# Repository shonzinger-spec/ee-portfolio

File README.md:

# EE Portfolio - Shon Zinger

Electrical engineering projects by Shon Zinger, a York University EE graduate. Each project is fully virtual and reproducible with free tools: a standalone Python model runs with numpy and matplotlib (project 06 also uses scipy), and the simulation, schematic and firmware checks are documented with real output pasted into the project README. No hardware was built.

## Start here

- 01 - [A small meter that shows how much power a gadget draws](01-smart-power-node/)
- 02 - [A power converter that steps 12 V down to 5 V, controlled by software](02-sync-buck/)
- 03 - [A program that draws a motor start/stop wiring diagram from a parts list](03-ladder-dxf/)
- 04 - [The protection circuit and firmware for a four-cell lithium-ion battery pack](04-smart-bms-sim/)
- 05 - [A brushless motor controller, tested against a software model of the motor](05-bldc-hil-sim/)
- 06 - [The signal processing of a fingertip blood-oxygen sensor, tested on synthetic signals](06-ppg-spo2/)
- 07 - [A risk calculator for a hypothetical insulin pump, using fault trees and Monte Carlo](07-fault-tree-risk/)

Each project folder has a plain-words summary at the top and the full evidence below.

| # | Project | What it shows | Verification |
|---|---|---|---|
| 01 | [Smart power-monitoring IoT node](01-smart-power-node/) | ESP32 + INA219 power monitor on a 5 V / 2 A rail with an SSD1306 display: 50 mOhm Kelvin shunt, register-level driver, two-task FreeRTOS firmware | main.py self-check, LTspice and ngspice 6/6, host test 33/33, KiCad ERC 0 errors, PCB DRC + schematic parity 0 violations (check_pcb.py 13/13), Wokwi live run |
| 02 | [Digital synchronous buck converter](02-sync-buck/) | 12 V to 5 V / 3 A, 200 kHz synchronous buck with discrete FETs, RC snubber and a digital PI loop in C (input and reference feed-forward, DPWM hysteresis, anti-windup, over-current latch) | main.py 59/59, LTspice vs ngspice cross-check, host test 19/19 + negative gate 4/4, KiCad ERC 0 errors |
| 03 | [Ladder-to-DXF schematic generator](03-ladder-dxf/) | NEMA/JIC motor-starter ladder drawn from a device list: automatic device tags, wire numbers and coil/contact cross-references, DXF for any CAD program, BOM and wire list in Excel | main.py self-check, pytest 22/22, ezdxf audit 0 errors |
| 04 | [Smart BMS simulator](04-smart-bms-sim/) | 4S Li-ion pack: equivalent-circuit and thermal-runaway cell model, BMS firmware in C with OV/UV/OCD/SCD/temperature protection, coulomb-counting SoC, passive balancing and a cell-level end of charge | main.py 30/30, host test 34/34 + negative gate 6/6, ngspice 128 corners, KiCad ERC 0 errors |
| 05 | [BLDC motor controller, hardware-in-the-loop](05-bldc-hil-sim/) | 24 V BLDC with Hall 6-step commutation: timer-interrupt PWM in C with firmware dead-time insertion, cascaded speed/current PI on a sampled DC-link shunt, over-current/Hall/stall protection, run against a switch-level inverter and motor model | main.py 26/26, host test 33/33 + negative gate 7/7, ngspice dead-time sweep and full inverter (within 1.5 % of the plant), KiCad ERC 0 errors |
| 06 | [PPG pulse-oximetry engine](06-ppg-spo2/) | Red/IR photoplethysmography DSP in Python: synthetic signals with room-light flicker and motion, ambient subtraction, AC/DC filters, beat tracking with quality checks, ratio-of-ratios calibration fitted on one synthetic desaturation cohort and tested on another, SpO2 and pulse rate with status flags | main.py 28/28, pytest 47/47, negative gate 10/15 (the five overlapping motion checks are caught together), A_rms 1.34 % on 10 held-out synthetic subjects (ISO 80601-2-61 limit 4.0 %) |
| 07 | [Fault tree and Monte Carlo risk simulator](07-fault-tree-risk/) | ISO 14971 style quantitative risk analysis of a hypothetical insulin pump in Python: fault tree with vote gates and common cause, exact BDD probabilities, drift / wear-out / latent-fault models, Monte Carlo of component state transitions for hazard rates and MTBF, risk evaluation before and after one risk control | main.py 23/23, pytest 68/68, negative gate 15/15, Monte Carlo cross-checked against analytic and Markov results (MTBF 12901 h exact vs 12878 h simulated) |

Highlights of project 01:

- INA219 high-side current sensing: shunt sizing, PGA and calibration choices, saturation handling
- FreeRTOS on the ESP32: two pinned tasks, an overwrite-queue mailbox, a mutex-protected I2C bus
- KiCad schematic generated by script, checked with ERC and a netlist check
- Shunt front-end simulated in LTspice and cross-checked in ngspice
- Wokwi live run of the unmodified firmware against a custom INA219 chip model

## Repository conventions

- A dedicated folder per project (`NN-name/`).
- A standalone main file (for example `main.py`) that runs without a complex install chain.
- A Verification section in each project README, with plots, logs and metrics pasted from real runs.
- A three-sentence Engineering why on the project's trade-offs.
- A Credits section stating what the author did and where AI assisted.

Author: Shon Zinger

AI assistance: Claude (Anthropic) helped with parts of each project; the Credits section of each project README says which.

License: MIT, see [LICENSE](LICENSE).

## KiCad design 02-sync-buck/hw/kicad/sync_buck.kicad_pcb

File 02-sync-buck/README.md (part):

# 02 - Digital Synchronous Buck Converter (12 V to 5 V / 3 A)

## In plain words

- **What it is:** a power converter that steps 12 V down to 5 V, like the adapter that turns a car's supply into a phone charge, but with the control loop done in software on a microcontroller (a small programmable chip).
- **Why it matters:** converters like this sit inside nearly every electronic product, and wasting less power as heat means smaller, cooler devices.
- **What was done:** I designed the circuit, wrote the control code in C and laid out the PCB (the green circuit board), then tested them in circuit simulators and software tests. It is simulated only: no hardware was built.
- **Headline result:** in simulation the output ripple is 9 mV p-p and the efficiency is 97.3 % at 3 A (power stage only, gate drive excluded).
- **Try it:** `python3 main.py`

A simulated design of a digitally controlled synchronous buck: 12 V in, 5 V out at up to 3 A, 200 kHz, two discrete 40 V N-MOSFETs driven by a UCC27211 half-bridge driver, 15 uH / 470 uF output filter, RC snubber on the switch node, and an ESP32-class controller closing the loop in C. The controller samples the output (10k / 6.8k divider), the load current (5 mOhm shunt + INA181A3) and the input voltage (47k / 10k divider) at 50 kHz and runs a PI loop on volts with input-voltage and reference feed-forward, an integrator dead band, DPWM hysteresis, anti-windup, a pre-bias-safe soft start and a latching over-current trip. The ESP32 firmware around that controller compiles. A simulator build of it ran on a simulated ESP32 in Wokwi against the host test's power-stage model: soft start, load steps and an over-current trip. The board is laid out in KiCad: 2 layers, DRC clean, Gerbers and drill files exported. Everything is simulation, host tests and design files; no hardware was built.

| Item | Value |
|---|---|
| Input / output | 12 V (10.8 to 13.2 V) / 5.0 V, 3 A |
| Switching | 200 kHz, 400-tick DPWM (80 MHz MCPWM timer), 50 ns dead time |
| Power stage | 2 x 40 V N-MOSFET (about 7 mOhm), 15 uH (DCR 20 mOhm, Isat 6 A), 470 uF polymer + 10 uF X7R, 1.8 ohm + 1 nF snubber |
| Control | PI on volts, Kp 0.02 V/V, Ki 800 V/(V s), 50 kHz, crossover 128 Hz, PM 89 deg, GM 9.1 dB at no load |
| Simulated results | ripple 9 mV p-p, efficiency 97.3 % at 3 A and 98.3 % at 1 A (power stage, gate drive excluded), 2.5 A load step -8.3 % / +8.8 %, recovery 1.3 ms / 2.1 ms |
| Firmware | ESP32, Arduino-ESP32 core 3.2.0. Product build: MCPWM outputs with 50 ns hardware dead time, ADC1 sampling, 50 kHz control task on core 1, over-current and overrun latches (compile-only; never executed, not even in simulation). LEDC build for Wokwi |
| On-target run (Wokwi) | LEDC sim build at 20x time dilation (times are control time): soft start within +/-1 % in 5.4 ms; 0.5 -> 3 -> 0.5 A steps inside +/-10 %; 6.25 A overload: OCP latched 40 us after the first over-limit sample (3 samples) with both gates low; 0 shoot-through in 375,364 dead times |
| PCB | 54 x 40 mm, 2 layers, 1 oz. DRC: 0 violations, 0 unconnected, 0 parity errors. Layout checks: 39/39 (23 of them on sabotaged copies). Gerbers and Excellon drill files |

## Quick start

Python 3.9+ with numpy and matplotlib. The model needs no SPICE, simulator or hardware.

```
pip install numpy matplotlib
python3 main.py
```

It prints a PASS/FAIL self-check (design equations, the model against the LTspice and ngspice logs, LTspice against ngspice, the digital loop margins, and a Python port of the controller against the C host test) and writes docs/img/main_py_buck.png; add `--no-plot` to skip the figure.

Other checks, from this folder:

```
sh sim/run_spice.sh                 # LTspice + ngspice 47, logs to docs/ (about 50 s)
make -C test/host test              # controller host test, model in the loop
make -C test/host negative          # the same test against four broken controllers
cd hw/kicad && python3 gen_schematic.py --export && python3 check_netlist.py
```

Firmware (arduino-cli 1.2.0 with the esp32:esp32 core 3.2.0), from this folder. The first command builds the product (MCPWM). The second builds the Wokwi variant (LEDC) into sim/wokwi/build:

```
arduino-cli compile -b esp32:esp32:esp32 --warnings all --clean --library src/buck_ctrl src/buck_esp32
arduino-cli compile -b esp32:esp32:esp32 --warnings all --clean --library src/buck_ctrl \
  --build-property "compiler.cpp.extra_flags=-DBUCK_PWM_LEDC" \
  --build-property "compiler.c.extra_flags=-DBUCK_PWM_LEDC" \
  --output-dir sim/wokwi/build src/buck_esp32
```

On-target run in Wokwi. It needs a WASI-SDK clang for the power-stage chip and your own free Wokwi CI token. See [sim/wokwi/README_WOKWI.md](sim/wokwi/README_WOKWI.md):

```
sim/wokwi/build_chip.sh --web
cd sim/wokwi && WOKWI_CLI_TOKEN=... wokwi-cli . --scenario buck_steps.test.yaml --timeout 4000 --serial-log-file ../../docs/wokwi_serial.log
```

PCB. Run these with KiCad 10's bundled Python, which provides `pcbnew`; on macOS it is /Applications/KiCad/KiCad.app/Contents/Frameworks/Python.framework/Versions/3.9/bin/python3:

```
cd hw/kicad && python3 gen_pcb.py --export   # board, DRC, Gerbers, drill files, renders
python3 check_pcb.py                          # layout checks and sabotaged copies
```

## Engineering why

The 15 uH inductor keeps ripple at 32 % of the 3 A load and the peak at 3.5 A against a 6 A saturation rating, but the 470 uF output capacitor is sized for load steps rather than the 9 mV ripple, because a PI loop sampled at 50 kHz has to cross over near 130 Hz, far below the 1.9 kHz LC resonance, so the first millisecond of a 2.5 A step is carried by the filter's 0.18 ohm characteristic impedance (an 8 % dip) and not by the controller. Running the PI on volts with input-voltage and reference feed-forward keeps the loop gain constant from 10.8 to 13.2 V and lets soft start follow its ramp, while a 20 mV integrator dead band and 0.75 LSB of duty hysteresis stop the 30 mV DPWM step from pumping that resonance into a limit cycle, at the cost of up to about 20 mV of static error. On the switch node, 40 V FETs and a 1.8 ohm + 1 nF snubber spend about 40 mW (0.3 points of efficiency) to cut the simulated ringing peak from 27.9 V to 22.2 V in LTspice (22.8 V to 20.1 V in ngspice), leaving more than 40 % margin to the 40 V rating.

## Verification

Each block below is copied from the log named above it and was produced by the command shown. All runs were on macOS. The model, SPICE and host-test runs are from 2026-10-27. The schematic ERC, firmware, Wokwi and PCB runs are from 2026-11-03. Everything is simulation, host tests and design checks; no hardware was built.

### Standalone model (main.py)

`python3 main.py` (docs/main_py.log). Exit code 0 means every check passed.

```
Sync buck 02 - main.py (simulated design; no hardware built)
Constants from src/buck_ctrl/buck_config.h: Kp 0.02 V/V, Ki 800 V/(V s), Ts 20 us, DPWM 400 ticks, dead band 20 mV, hysteresis 0.75 LSB

[1] Netlist and firmware constants
  C01 model values = sim/buck_sync.cir           D, L, C7, ESR, DCR, Rsh, dead time           PASS
  C02 firmware fsw / ticks / dead time           200 kHz, 400 ticks, 4 x 12.5 ns = 50 ns      PASS

[2] Design equations (3 A, 12 V)
    D = 0.4167, dIL = 0.972 A p-p (32 % of 3 A), Ipk = 3.49 A, f0 = 1876 Hz, Z0 = 0.177 ohm
  C03 inductor ripple 20-40 % of Iout            32 %                                         PASS
  C04 Ipk <= Isat / 1.2                          3.49 A vs 5.00 A                             PASS
  C05 2.5 A step: Z0 * dI <= 10 % Vout           442 mV (limit 500 mV)                        PASS
  C06 LC resonance > 10 x loop crossover         f0 1876 Hz, fc 127 Hz                        PASS

[3] LTspice vs ngspice (cases: 1 = 3 A, 2 = 1 A, 3 = 3 A no snubber)
  C07 vout_avg case 1                            LT 4.9613  ng 4.965  rel 0.0752 %            PASS
  C07 vout_avg case 2                            LT 5.0457  ng 5.047  rel 0.0272 %            PASS
  C07 il_pp case 1                               LT 0.97635  ng 0.97772  rel 0.14 %           PASS
  C07 il_pp case 2                               LT 0.97872  ng 0.97857  rel 0.0155 %         PASS
  C07 vout_pp case 1                             LT 0.0091524  ng 0.0092951  rel 1.56 %       PASS
  C07 vout_pp case 2                             LT 0.0089283  ng 0.0089842  rel 0.626 %      PASS
  C07 pin case 1                                 LT 15.186  ng 15.207  rel 0.135 %            PASS
  C07 pin case 2                                 LT 5.1814  ng 5.1807  rel 0.0118 %           PASS
  C07 pout case 1                                LT 14.768  ng 14.791  rel 0.15 %             PASS
  C07 pout case 2                                LT 5.0917  ng 5.0945  rel 0.0544 %           PASS
  C07 eff case 1                                 LT 0.9725  ng 0.97264  abs 0.000146          PASS
  C07 eff case 2                                 LT 0.98271  ng 0.98336  abs 0.000651         PASS
  C07 pgate case 1                               LT 0.095451  ng 0.095092  rel 0.376 %        PASS
  C07 pgate case 2                               LT 0.095232  ng 0.095293  rel 0.0637 %       PASS
  C08 LTspice Vsw peak < 0.75 BVdss              max 27.9 V (limit 30 V)                      PASS
  C09 LTspice snubber lowers the Vsw peak        22.2 V with, 27.9 V without                  PASS
  C08 ngspice Vsw peak < 0.75 BVdss              max 22.8 V (limit 30 V)                      PASS
  C09 ngspice snubber lowers the Vsw peak        20.1 V with, 22.8 V without                  PASS

[4] Model vs SPICE
  C10 Vout full 3 A vs LT                        model 4.9619 V, SPICE 4.9613 V               PASS
  C11 dIL p-p full 3 A vs LT                     model 0.981 A, SPICE 0.976 A                 PASS
  C12 Vout ripple full 3 A vs LT                 model 8.91 mV, SPICE 9.15 mV                 PASS
  C13 efficiency full 3 A vs LT                  model 97.34 %, SPICE 97.25 %                 PASS
  C14 gate drive full 3 A vs LT                  model 87 mW, SPICE 95 mW                     PASS
  C15 snubber loss full 3 A vs LT                C Vin^2 fsw 28.8 mW (+/-50 %), SPICE 41.2 mW PASS
  C10 Vout full 3 A vs ng                        model 4.9619 V, SPICE 4.9650 V               PASS
  C11 dIL p-p full 3 A vs ng                     model 0.981 A, SPICE 0.978 A                 PASS
  C12 Vout ripple full 3 A vs ng                 model 8.91 mV, SPICE 9.30 mV                 PASS
  C13 efficiency full 3 A vs ng                  model 97.34 %, SPICE 97.26 %                 PASS
  C14 gate drive full 3 A vs ng                  model 87 mW, SPICE 95 mW                     PASS
  C15 snubber loss full 3 A vs ng                C Vin^2 fsw 28.8 mW (+/-50 %), SPICE 36.7 mW PASS
    loss budget at 3 A (mW): HS conduction 26, LS conduction 34, inductor DCR 179, shunt 44, Cin ESR 6, Cout ESR 1, HS switching 11, dead-time diode 45, reverse recovery 30, snubber 29
  C16 FET Tj at 50 degC ambient < 100 degC       HS 66 mW, LS 79 mW -> Tj 54 degC             PASS
  C17 inductor temperature < 100 degC            179 mW -> 57 degC                            PASS
  C10 Vout light 1 A vs LT                       model 5.0272 V, SPICE 5.0457 V               PASS
  C11 dIL p-p light 1 A vs LT                    model 0.979 A, SPICE 0.979 A                 PASS
  C12 Vout ripple light 1 A vs LT                model 8.94 mV, SPICE 8.93 mV                 PASS
  C13 efficiency light 1 A vs LT                 model 98.27 %, SPICE 98.27 %                 PASS
  C14 gate drive light 1 A vs LT                 model 87 mW, SPICE 95 mW                     PASS
  C15 snubber loss light 1 A vs LT               C Vin^2 fsw 28.8 mW (+/-50 %), SPICE 24.5 mW PASS
  C10 Vout light 1 A vs ng                       model 5.0272 V, SPICE 5.0470 V               PASS
  C11 dIL p-p light 1 A vs ng                    model 0.979 A, SPICE 0.979 A                 PASS
  C12 Vout ripple light 1 A vs ng                model 8.94 mV, SPICE 8.98 mV                 PASS
  C13 efficiency light 1 A vs ng                 model 98.27 %, SPICE 98.34 %                 PASS
  C14 gate drive light 1 A vs ng                 model 87 mW, SPICE 95 mW                     PASS
  C15 snubber loss light 1 A vs ng               C Vin^2 fsw 28.8 mW (+/-50 %), SPICE 24.7 mW PASS

[5] Digital loop (PI + feed-forward, 50 kHz, 1-sample delay)
  C18 margins 0.01 A                             fc 128 Hz, PM 89 deg, GM 9.1 dB              PASS
  C18 margins 1 A                                fc 127 Hz, PM 89 deg, GM 10.5 dB             PASS
  C18 margins 3 A                                fc 126 Hz, PM 89 deg, GM 12.9 dB             PASS
  C18 margins 0.01 A, L +20 %                    fc 128 Hz, PM 89 deg, GM 7.6 dB              PASS
  C18 margins 0.01 A, C -20 %                    fc 128 Hz, PM 90 deg, GM 8.9 dB              PASS
  C18 margins 0.01 A, L -20 % C +20 %            fc 128 Hz, PM 89 deg, GM 11.0 dB             PASS

[6] Python port of the controller vs the C host test
  C19 host test log RESULT all PASS              19/19                                        PASS
  C20 0.5 -> 3 A dip: Python vs C                Python 4.5864 V, C 4.5864 V                  PASS
  C21 3 -> 0.5 A peak: Python vs C               Python 5.4419 V, C 5.4419 V                  PASS

RESULT: 59/59 PASS
figure: docs/img/main_py_buck.png
```

*main.py: modelled inductor current and output ripple at 3 A (top left), efficiency from the loss budget with the LTspice and ngspice points (top right), digital loop gain at three loads (bottom left), and the Python port of the controller through soft start and the 2.5 A load steps (bottom right).*

### LTspice power stage

`sh sim/run_spice.sh` runs `LTspice -b sim/buck_sync.cir` (open loop, fixed duty 0.4195, three stepped cases: 1 = 3 A, 2 = 1 A, 3 = 3 A without snubber, measured over 1.00 to 1.05 ms after starting from the settled operating point). Measurement section of docs/sim_ltspice.log (the script converts LTspice's UTF-16 log to UTF-8):

```
Measurement: vout_avg
  step	AVG(v(vload))	FROM	TO
     1	4.96132	0.001	0.00105
     2	5.04566	0.001	0.00105
     3	4.95987	0.001	0.00105

Measurement: vout_pp
  step	PP(v(vload))	FROM	TO
     1	0.00915241	0.001	0.00105
     2	0.0089283	0.001	0.00105
     3	0.00914478	0.001	0.00105

Measurement: il_avg
  step	AVG(i(l1))	FROM	TO
     1	2.97249	0.001	0.00105
     2	1.00848	0.001	0.00105
     3	2.97174	0.001	0.00105

Measurement: il_pp
  step	PP(i(l1))	FROM	TO
     1	0.976345	0.001	0.00105
     2	0.978718	0.001	0.00105
     3	0.976289	0.001	0.00105

Measurement: pin
  step	AVG(-v(vsrc)*i(v1))	FROM	TO
     1	15.1862	0.001	0.00105
     2	5.18135	0.001	0.00105
     3	15.1747	0.001	0.00105

Measurement: pout
  step	AVG(v(vload)*v(vload)/rload)	FROM	TO
     1	14.7685	0.001	0.00105
     2	5.09174	0.001	0.00105
     3	14.7599	0.001	0.00105

Measurement: pgate
  step	AVG(-(v(ghd,sw)*i(vgh)+v(gld)*i(vgl)))	FROM	TO
     1	0.0954512	0.001	0.00105
     2	0.0952321	0.001	0.00105
     3	0.0945081	0.001	0.00105

Measurement: psnub
  step	AVG(v(sw,snb)*i(rsn))	FROM	TO
     1	0.0411916	0.001	0.00105
     2	0.0244952	0.001	0.00105
     3	6.20517e-10	0.001	0.00105

Measurement: vsw_max
  step	MAX(v(sw))	FROM	TO
     1	22.2205	0.001	0.00105
     2	17.8984	0.001	0.00105
     3	27.9306	0.001	0.00105

Measurement: eff
  step	pout/pin
     1	0.972498
     2	0.982705
     3	0.972665
```

### ngspice 47 cross-check

The same circuit and VDMOS card in ngspice dialect (sim/ngspice/buck_sync_ngspice.cir): the `.step`/`table()` sweep becomes a control-block loop with `alterparam` + `reset`, and the measurements move into the control block. Measurement lines of docs/sim_ngspice.log (`grep -E "^step|^[a-z_]+ += " docs/sim_ngspice.log`):

```
step 1 RLOAD=1.6667 SNUB=1
vout_avg            =  4.96505e+00 from=  1.00000e-03 to=  1.05000e-03
vout_pp             =  9.29507e-03 from=  1.00000e-03 to=  1.05000e-03
il_avg              =  2.97308e+00 from=  1.00000e-03 to=  1.05000e-03
il_pp               =  9.77716e-01 from=  1.00000e-03 to=  1.05000e-03
pin                 =  1.52067e+01 from=  1.00000e-03 to=  1.05000e-03
pout                =  1.47907e+01 from=  1.00000e-03 to=  1.05000e-03
pgate               =  9.50925e-02 from=  1.00000e-03 to=  1.05000e-03
psnub               =  3.66659e-02 from=  1.00000e-03 to=  1.05000e-03
vsw_max             =  2.01266e+01 at=  1.04506e-03
eff = 0.972644
step 2 RLOAD=5 SNUB=1
vout_avg            =  5.04703e+00 from=  1.00000e-03 to=  1.05000e-03
vout_pp             =  8.98421e-03 from=  1.00000e-03 to=  1.05000e-03
il_avg              =  1.00808e+00 from=  1.00000e-03 to=  1.05000e-03
il_pp               =  9.78566e-01 from=  1.00000e-03 to=  1.05000e-03
pin                 =  5.18074e+00 from=  1.00000e-03 to=  1.05000e-03
pout                =  5.09451e+00 from=  1.00000e-03 to=  1.05000e-03
pgate               =  9.52928e-02 from=  1.00000e-03 to=  1.05000e-03
psnub               =  2.47471e-02 from=  1.00000e-03 to=  1.05000e-03
vsw_max             =  1.76416e+01 at=  1.02006e-03
eff = 0.983356
step 3 RLOAD=1.6667 SNUB=0
vout_avg            =  4.96347e+00 from=  1.00000e-03 to=  1.05000e-03
vout_pp             =  9.22277e-03 from=  1.00000e-03 to=  1.05000e-03
il_avg              =  2.97294e+00 from=  1.00000e-03 to=  1.05000e-03
il_pp               =  9.77638e-01 from=  1.00000e-03 to=  1.05000e-03
pin                 =  1.52103e+01 from=  1.00000e-03 to=  1.05000e-03
pout                =  1.47813e+01 from=  1.00000e-03 to=  1.05000e-03
pgate               =  9.47475e-02 from=  1.00000e-03 to=  1.05000e-03
psnub               =  4.67871e-12 from=  1.00000e-03 to=  1.05000e-03
vsw_max             =  2.27861e+01 at=  1.01506e-03
eff = 0.971796
```

main.py compares the two simulators (check group [3] above): Vout within 0.08 %, inductor ripple within 0.14 %, output ripple within 1.6 %, efficiency within 0.07 points, gate-drive power within 0.4 %. The switch-node peaks differ (27.9 V vs 22.8 V without snubber) because the ringing lasts a few nanoseconds and each simulator resolves it with its own time-step control; both stay below 30 V (75 % of BVdss) and both show the snubber lowering the peak.

### Controller host test (model in the loop)

`make -C test/host test` (docs/host_test.log). The controller (src/buck_ctrl) is compiled for the host with `-Wall -Wextra -Werror` and run against an averaged model of the power stage (test/host/plant.c, same component values as the SPICE decks), with 12-bit ADC quantisation, the 1 nF anti-alias filter, the 400-tick DPWM and a one-period computation delay.

```
./build/test_buck
02 sync buck controller - host test (model in the loop)
Kp 0.02 V/V, Ki 800 V/(V s), Ts 20 us, DPWM 400 ticks, dead band 20 mV, DPWM hysteresis 0.75 LSB, OCP 4.5 A x 3
# closed loop: soft start at 1 A, Vin 12 V
PASS startup overshoot <= 2 %         max 5.0271 V (limit 5.10 V)
PASS startup settle +/-1 % <= 8 ms    5.26 ms (limit 8 ms)
# steady state 1 A, 12-20 ms
PASS dc error <= 0.5 %                mean 5.0081 V (target 5.0 V)
PASS no limit cycle (duty steady)     0 duty-code changes (limit 0)
PASS low-frequency p-p <= 5 mV        0.00 mV (limit 5 mV)
# load step 0.5 -> 3 A at 30 ms, release 3 -> 0.5 A at 45 ms
PASS step dip >= 4.50 V (-10 %)       min 4.5864 V (limit 4.50 V)
PASS step recovery +/-1 % <= 5 ms     1.30 ms (limit 5 ms)
PASS release peak <= 5.50 V (+10 %)   max 5.4419 V (limit 5.50 V)
PASS release recovery +/-1 % <= 5 ms  2.10 ms (limit 5 ms)
# line ramps at 1 A: 12 -> 10.8 V at 65 ms, 10.8 -> 13.2 V at 80 ms (1 ms each)
PASS line deviation <= 2 %            80.8 mV (limit 100 mV)
PASS line recovery +/-1 % <= 5 ms     0.86 ms (limit 5 ms)
# overload 0.8 ohm (6.25 A) at 100 ms
PASS OCP latches within 3 samples     3 samples (limit 3)
PASS inductor peak < Isat 6 A         2.19 A (limit 6.0 A)
PASS stays off after the trip         duty 0, state 3
# unit: integrator windup (output held at 0 V for 20 ms, then 5.5 V)
PASS Vref + integrator <= Dmax x Vin  10.800 V (limit 10.80 V)
PASS unwinds to 50 % within 1.1 x bound 11.96 ms (limit 13.17 ms)
# unit: OCP needs consecutive samples, then latches
PASS 2 + 2 split samples: no trip     state 2 (fault = 3)
PASS 3rd sample trips, start ignored  state 3, fault code 1
# unit: pre-biased start
PASS soft start begins at 3 V pre-bias vref 3.000 V (expected 3.0 V)
RESULT: 19/19 PASS
```

### Negative gate

`make -C test/host negative` (docs/host_negative.log) builds four broken controllers and passes only if the host test fails against every one: M1 without the integrator dead band (limit cycle), M2 with both anti-windup lines deleted (the integrator winds up to 75 V), M3 with the over-current trip out of reach (the inductor reaches 9.7 A), M4 with plain rounding instead of DPWM hysteresis (the load release rings for about 10 ms).

```
== mutant m1 ==
FAIL no limit cycle (duty steady)     5 duty-code changes (limit 0)
FAIL low-frequency p-p <= 5 mV        76.42 mV (limit 5 mV)
RESULT: 17/19 PASS
mutant m1: test FAILED as required
== mutant m2 ==
FAIL Vref + integrator <= Dmax x Vin  74.980 V (limit 10.80 V)
FAIL unwinds to 50 % within 1.1 x bound 40.00 ms (limit 13.17 ms)
RESULT: 17/19 PASS
mutant m2: test FAILED as required
== mutant m3 ==
FAIL OCP latches within 3 samples     -1 samples (limit 3)
FAIL inductor peak < Isat 6 A         9.65 A (limit 6.0 A)
FAIL stays off after the trip         duty 157, state 2
FAIL 3rd sample trips, start ignored  state 1, fault code 0
RESULT: 15/19 PASS
mutant m3: test FAILED as required
== mutant m4 ==
FAIL release recovery +/-1 % <= 5 ms  9.72 ms (limit 5 ms)
RESULT: 18/19 PASS
mutant m4: test FAILED as required
NEGATIVE GATE: 4/4 mutants caught
```

### KiCad ERC and netlist check

`cd hw/kicad && python3 gen_schematic.py --export`, then `kicad-cli sch erc` and `python3 check_netlist.py` (docs/kicad_erc.log; the ERC report also lists four checks set to ignore, as in project 01):

```
# cmd: cd hw/kicad && python3 gen_schematic.py --export
# cmd: kicad-cli sch erc --severity-all -o erc.rpt sync_buck.kicad_sch
# cmd: python3 check_netlist.py
 ** ERC messages: 0  Errors 0  Warnings 0
    - Global label only appears once in the schematic
    - Four connection points are joined together
    - SPICE model issue
    - Assigned footprint doesn't match footprint filters
PASS VIN      C1.1 C2.1 C3.1 C4.1 J1.1 Q1.2 R12.1 U1.1
PASS GND      C1.2 C10.2 C11.2 C12.2 C2.2 C3.2 C4.2 C6.2 C7.2 C8.2 C9.2 J1.2 J2.2 J3.2 Q2.3 R10.2 R11.2 R13.2 R4.2 R8.2 U1.7 U2.2 U2.5
PASS SW       C5.2 L1.1 Q1.3 Q2.2 R3.2 R5.1 U1.4
PASS GH       Q1.1 R1.2 R3.1
PASS GL       Q2.1 R2.2 R4.1
PASS HO       R1.1 U1.3
PASS LO       R2.1 U1.8
PASS HB       C5.1 U1.2
PASS SNB      C6.1 R5.2
PASS VOUT     C7.1 C8.1 L1.2 R6.1
PASS SH_P     R6.2 U2.3
PASS SH_N     R6.3 U2.4
PASS VLOAD    J2.1 R6.4 R7.1
PASS VSENSE   C10.1 J3.5 R7.2 R8.1
PASS VINSENSE C12.1 J3.7 R12.2 R13.1
PASS IAMP     R9.1 U2.1
PASS ISENSE   C11.1 J3.6 R9.2
PASS PWM_H    J3.3 R10.1 U1.5
PASS PWM_L    J3.4 R11.1 U1.6
PASS +3V3     C9.1 J3.1 U2.6
info: 0 single-pin nets (expected 0)
RESULT: PASS
```

*Schematic: KiCad 10, generated by hw/kicad/gen_schematic.py, ERC 0 errors / 0 warnings, netlist check PASS on every net.*

### ESP32 firmware build

The controller is compiled from src/buck_ctrl as a library: one copy, unmodified. With `--warnings all` the compiler prints no warnings for either build. The product build (MCPWM) is in docs/fw_compile_mcpwm.log:

```
# arduino-cli 1.2.0 (esp32:esp32 core 3.2.0), Tue Nov  3 14:16:39 EST 2026
arduino-cli  Version: 1.2.0 Commit: 9c495211 Date: 2025-02-24T15:57:28Z
# cmd: arduino-cli compile -b esp32:esp32:esp32 --warnings all --clean --library src/buck_ctrl src/buck_esp32
Sketch uses 324302 bytes (24%) of program storage space. Maximum is 1310720 bytes.
Global variables use 49348 bytes (15%) of dynamic memory, leaving 278332 bytes for local variables. Maximum is 327680 bytes.
EXIT=0
```

The Wokwi build (LEDC) is in docs/fw_compile_ledc.log. The log ends with a check that the binary rebuilt after the negative runs below matches the one the passing run used:

```
# arduino-cli 1.2.0 (esp32:esp32 core 3.2.0), Tue Nov  3 14:16:14 EST 2026
arduino-cli  Version: 1.2.0 Commit: 9c495211 Date: 2025-02-24T15:57:28Z
# cmd: arduino-cli compile -b esp32:esp32:esp32 --warnings all --clean --library src/buck_ctrl --build-property "compiler.cpp.extra_flags=-DBUCK_PWM_LEDC" --build-property "compiler.c.extra_flags=-DBUCK_PWM_LEDC" --output-dir sim/wokwi/build src/buck_esp32
Sketch uses 313682 bytes (23%) of program storage space. Maximum is 1310720 bytes.
Global variables use 49532 bytes (15%) of dynamic memory, leaving 278148 bytes for local variables. Maximum is 327680 bytes.
EXIT=0
# restore check (Tue Nov  3 14:16:39 EST 2026): cmp of the rebuilt sim/wokwi/build/buck_esp32.ino.bin against the binary that was in place before these runs (the one docs/wokwi_run.log ran):
#   sizes 313824 / 313824 bytes, differing bytes: 70
#   the 70 bytes are at offsets 177-208 (app ELF SHA-256 field), 2671-2677 (build time string) and 313792-313824 (image checksum and SHA-256 trailer); the code and data are identical
```

### On-target run in Wokwi (simulated ESP32)

The LEDC build runs on Wokwi's simulated ESP32 (wokwi-cli 0.29.1).

**The power stage.** It is a Wokwi custom chip, sim/wokwi/buck_plant.chip.c. The chip includes the host test's plant.c, so the run uses the same averaged model and component values as `make -C test/host test`. It works as follows:
- It reads the PWM_H and PWM_L edges.
- It averages each 6.4 us LEDC period into a switch-node voltage. A both-off gap longer than 100 ns lets the body diodes conduct.
- It drives VSENSE, ISENSE and VINSENSE into the ADC pins.
- It measures every dead time and latches its FLT pin on any H/L overlap.

**The scenario.** sim/wokwi/buck_steps.test.yaml repeats the host test:
1. Soft start at 1 A.
2. Load 0.5 -> 3 -> 0.5 A.
3. An overload of 6.25 A, which must latch the OCP with both gates low.

**Time scaling.** Wokwi runs this firmware much slower than real time. One control update costs about 91 us of simulated time. With the 50 kHz interrupt it costs about 500 us (docs/wokwi_timing_diag.log). So the Wokwi build changes the timing:
- The firmware paces the loop on the CPU cycle counter, once every 20 us x 20 of simulated time.
- The chip steps its plant by dt / 20.

Controller and plant therefore still see one update per 20 us. Every firmware time below is control time.

**The ADC.** The Wokwi build reads the ADC through Wokwi's 5 V transfer, one pipelined conversion per update. sim/wokwi/README_WOKWI.md gives the measurements behind each change. None of these changes is in the product build.

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
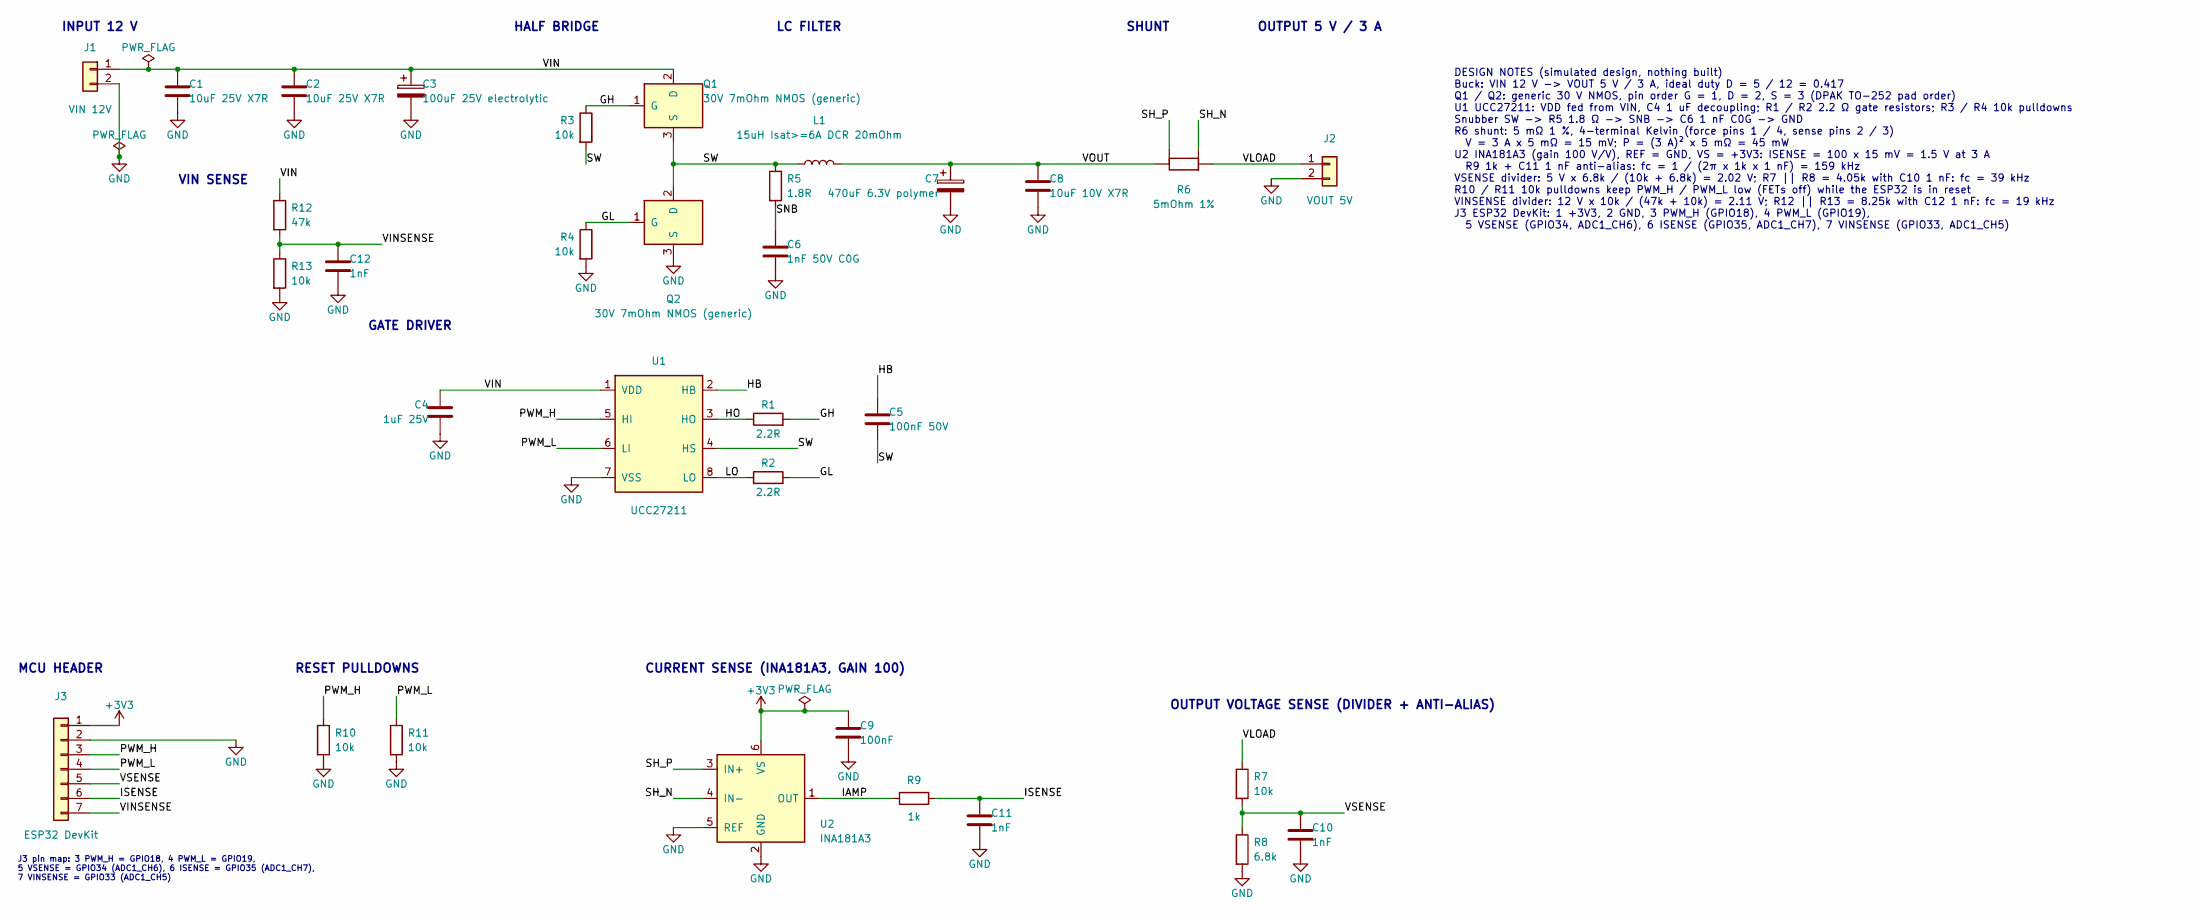
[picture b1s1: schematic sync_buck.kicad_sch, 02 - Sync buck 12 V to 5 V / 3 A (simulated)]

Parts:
C1, C2: 10uF 25V X7R; C_1210_3225Metric
C3: 100uF 25V electrolytic; CP_Radial_D8.0mm_P3.50mm
C4: 1uF 25V; C_0603_1608Metric
C5: 100nF 50V; C_0603_1608Metric
C6: 1nF 50V C0G; C_0603_1608Metric
C7: 470uF 6.3V polymer; CP_Elec_6.3x7.7
C8: 10uF 10V X7R; C_0805_2012Metric
C9: 100nF; C_0603_1608Metric
C10, C11, C12: 1nF; C_0603_1608Metric
J1: VIN 12V; PinHeader_1x02_P2.54mm_Vertical
J2: VOUT 5V; PinHeader_1x02_P2.54mm_Vertical
J3: ESP32 DevKit; PinHeader_1x07_P2.54mm_Vertical
L1: 15uH Isat>=6A DCR 20mOhm; L_Bourns_SRP1245A
Q1, Q2: 30V 7mOhm NMOS (generic); TO-252-3_TabPin2
R1, R2: 2.2R; R_0603_1608Metric
R3, R4, R7, R10, R11, R13: 10k; R_0603_1608Metric
R5: 1.8R; R_0603_1608Metric
R6: 5mOhm 1%; R_Shunt_Vishay_WSK2512_6332Metric_T1.19mm
R8: 6.8k; R_0603_1608Metric
R9: 1k; R_0603_1608Metric
R12: 47k; R_0603_1608Metric
U1: UCC27211; SOIC-8_3.9x4.9mm_P1.27mm
U2: INA181A3; SOT-23-6

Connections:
+3V3: C9.1, J3.1, U2.6 (VS)
/GH: Q1.1 (G), R1.2, R3.1
/GL: Q2.1 (G), R2.2, R4.1
/HB: C5.1, U1.2 (HB)
/HO: R1.1, U1.3 (HO)
/IAMP: R9.1, U2.1 (OUT)
/ISENSE: C11.1, J3.6, R9.2
/LO: R2.1, U1.8 (LO)
/PWM_H: J3.3, R10.1, U1.5 (HI)
/PWM_L: J3.4, R11.1, U1.6 (LI)
/SH_N: R6.3, U2.4 (IN-)
/SH_P: R6.2, U2.3 (IN+)
/SNB: C6.1, R5.2
/SW: C5.2, L1.1, Q1.3 (S), Q2.2 (D), R3.2, R5.1, U1.4 (HS)
/VIN: C1.1, C2.1, C3.1, C4.1, J1.1, Q1.2 (D), R12.1, U1.1 (VDD)
/VINSENSE: C12.1, J3.7, R12.2, R13.1
/VLOAD: J2.1, R6.4, R7.1
/VOUT: C7.1, C8.1, L1.2, R6.1
/VSENSE: C10.1, J3.5, R7.2, R8.1
GND: C1.2, C2.2, C3.2, C4.2, C6.2, C7.2, C8.2, C9.2, C10.2, C11.2, C12.2, J1.2, J2.2, J3.2, Q2.3 (S), R4.2, R8.2, R10.2, R11.2, R13.2, U1.7 (VSS), U2.2 (GND), U2.5 (REF)

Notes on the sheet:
INPUT 12 V
VIN SENSE
HALF BRIDGE
LC FILTER
SHUNT
OUTPUT 5 V / 3 A
GATE DRIVER
MCU HEADER
RESET PULLDOWNS
J3 pin map: 3 PWM_H = GPIO18, 4 PWM_L = GPIO19, 5 VSENSE = GPIO34 (ADC1_CH6), 6 ISENSE = GPIO35 (ADC1_CH7), 7 VINSENSE = GPIO33 (ADC1_CH5)
CURRENT SENSE (INA181A3, GAIN 100)
OUTPUT VOLTAGE SENSE (DIVIDER + ANTI-ALIAS)
DESIGN NOTES (simulated design, nothing built) Buck: VIN 12 V -> VOUT 5 V / 3 A, ideal duty D = 5 / 12 = 0.417 Q1 / Q2: generic 30 V NMOS, pin order G = 1, D = 2, S = 3 (DPAK TO-252 pad order) U1 UCC27211: VDD fed from VIN, C4 1 uF decoupling; R1 / R2 2.2 Ω gate resistors; R3 / R4 10k pulldowns Snu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

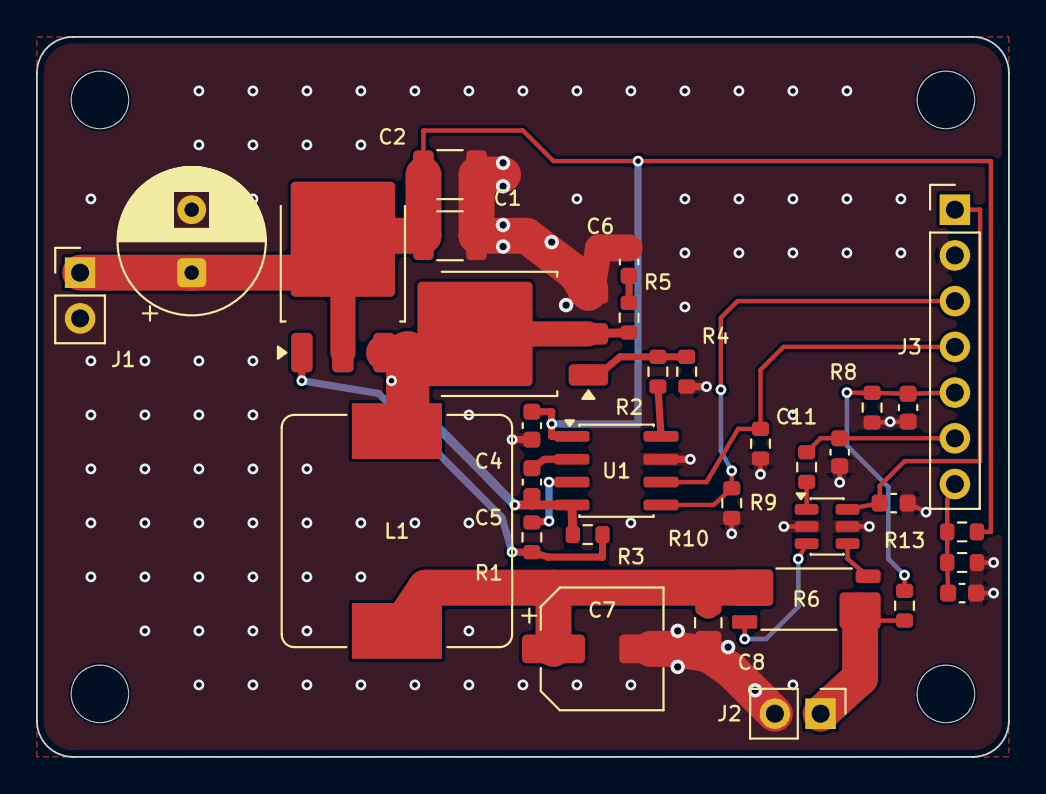
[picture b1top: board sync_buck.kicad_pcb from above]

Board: 2 copper layers, 54.0 x 40.0 mm, 37 parts (0 on the bottom side), 20 nets.

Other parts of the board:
H1, H2, H3, H4: MountingHole_3.2mm_M3

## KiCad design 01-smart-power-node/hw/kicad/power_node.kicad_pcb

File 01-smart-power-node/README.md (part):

# 01 - Smart Power-Monitoring IoT Node (ESP32 + INA219 + SSD1306)

## In plain words

- **What it is:** a small meter that shows how much power a gadget on a 5 V supply draws, built around an ESP32 (a low-cost Wi-Fi microcontroller) and an INA219 (a chip that measures current and voltage) with a small screen.
- **Why it matters:** products from power supplies to smart plugs need to know their own power draw to log it, limit it or warn about faults.
- **What was done:** I designed the measuring circuit, wrote the firmware (the code that runs on the chip) and laid out a PCB (the green circuit board), then checked it all in simulators and software tests. It is simulated only: no hardware was built.
- **Headline result:** at 2 A the 50 mOhm sensing resistor drops 100 mV, and the project's own self-check ends with RESULT: ALL PASS.
- **Try it:** `python3 main.py`

Monitors a 5 V rail at up to 2 A. A high-side 50 mOhm shunt feeds an INA219 set to PGA /4 (+/-160 mV full scale, 3.2 A range, 100 mV at 2 A), with Current_LSB 100 uA/bit, CAL = 8192 and Power_LSB 2 mW. Firmware runs FreeRTOS on the ESP32 Arduino core: sensorTask (priority 3) every 100 ms using vTaskDelayUntil, displayTask (priority 2) every 500 ms, both pinned to core 1. A length-1 queue with xQueueOverwrite/xQueuePeek acts as a latest-value mailbox. A mutex (priority inheritance) serialises the shared 400 kHz I2C bus. The INA219 driver is register-level; no INA219 library is used.

The carrier PCB is a 75 x 50 mm, 2-layer board (KiCad 10): the DevKitC plugs into sockets with its antenna past the board edge, and the 2 A path runs in 2.0 mm traces through the Kelvin-sensed shunt (see [PCB layout](#pcb-layout)).

## Quick start

Python 3.9+. The model needs only numpy and matplotlib: no SPICE, simulator or hardware.

```
pip install numpy matplotlib
python3 main.py
```

It prints a PASS/FAIL self-check (analog front-end against the SPICE netlist's expectations, INA219 readings against the live Wokwi run) and writes docs/img/main_py_frontend.png; add `--no-plot` to skip the figure.

## Engineering why

A 50 mOhm shunt trades resolution for burden: at 2 A it drops 100 mV (2 % of the 5 V rail) and dissipates 0.2 W, where 100 mOhm would double both for resolution the INA219's 12-bit ADC does not need. Choosing PGA /4 (+/-160 mV) leaves 60 % headroom above the 2 A design load, but with CAL = 8192 the chip's OVF bit can never fire, so the firmware treats a SHUNT register at +/-159.9 mV as saturated instead of reporting a clipped 3.2 A. In firmware, 64-sample averaging (about 68 ms per shunt + bus conversion) fits inside the 100 ms sensor period, and a length-1 overwrite queue hands the display the newest sample without blocking, at the cost of keeping no history.

## Verification

Each block below is copied from a log or from the command shown above it (run 2026-10-27 on macOS; the PCB build and checks 2026-11-03 on macOS with KiCad 10.0.7). Everything is simulation, host tests and design checks; no hardware was built.

### Standalone model (main.py)

`python3 main.py` reproduces the shunt front-end and the INA219 register chain without SPICE or hardware, then checks itself. Exit code 0 means every check passed.

```
Smart Power Node 01 - main.py
Constants (mirrored from src/power_node/config.h)
  R_shunt 0.05 ohm | rail 5 V | PGA /4 (+/-160 mV) | Current_LSB 100 uA
  CAL 8192 | Power_LSB 2 mW | saturation threshold 15990 counts (159.9 mV)
  CAL                    8192     expected 8192     PASS
  saturation threshold   15990    expected 15990    PASS
  Power_LSB mW           2        expected 2        PASS

Analog transient: 30001 points, 1 us grid, 0 to 30 ms, filter tau 2.0 us
check                expected     computed   rel err  result
Vsh_max                 0.1 V        0.1 V   0.0000%  PASS
Vina_max                0.1 V        0.1 V   0.0000%  PASS
Vload_min               4.9 V        4.9 V   0.0000%  PASS
Psh_pk                  0.2 W        0.2 W   0.0000%  PASS
Isense_pk                 2 A          2 A   0.0000%  PASS
Vsh_at_1p5 (9 ms)     0.075 V      0.075 V   0.0000%  PASS

INA219 digital model vs live Wokwi run (exact string match)
CSV fields: bus_V,shunt_mV,current_mA,power_mW
load     Wokwi                       model                       result
1000 mA  4.952,50.00,1000.0,4952.0   4.952,50.00,1000.0,4952.0   PASS
         registers: SHUNT=5000 BUS=1238 CURRENT=10000 POWER=2476
2000 mA  4.900,100.00,2000.0,9800.0  4.900,100.00,2000.0,9800.0  PASS
         registers: SHUNT=10000 BUS=1225 CURRENT=20000 POWER=4900
3200 mA  invalid (SENSOR ERR)        invalid (SENSOR ERR)        PASS
         registers: SHUNT=16000 BUS=1210 CURRENT=32000 POWER=7744

Saturation boundary (threshold 15990 counts)
3197 mA  SHUNT=15985  valid    PASS
3198 mA  SHUNT=15990  invalid  PASS
OVF unreachable: max CURRENT raw at full scale = 32000 <= 32767  PASS

Firmware samples every 100 ms: 1 sample falls inside the 30 ms profile (t = 0).
Figure written: docs/img/main_py_frontend.png (INA219 markers every 1 ms)

RESULT: ALL PASS
```

The Wokwi side of this comparison runs this repository's own INA219 chip model (sim/wokwi/ina219.chip.c), so the match confirms the firmware read-out path and the Python port of that model, not the behaviour of real INA219 silicon.

*main.py figure: load current with the INA219 CURRENT reading as markers (top); Vsh and the filtered V(inp,inn) in mV (bottom), with an inset on the 2 A ramp where the 2 us filter lag is visible. The firmware samples every 100 ms, which would put one sample (t = 0) inside this 30 ms profile, so the markers are spaced 1 ms apart.*

The digital model is instantaneous, like the Wokwi chip model. The real INA219 averages 64 conversions per channel in this configuration, so it would smear the 30 ms profile.

### LTspice shunt front-end

```
/Applications/LTspice.app/Contents/MacOS/LTspice -b sim/shunt_frontend.cir
```

Load profile: PWL steps 0 -> 0.5 -> 1.5 -> 2 -> 0.2 -> 0 A over 30 ms; 10 ohm + 10 ohm + 100 nF differential input filter. Measured values from docs/sim_ltspice.log.

| Check | Expected | Measured | PASS |
|---|---|---|---|
| Vsh_max | 100 mV | 0.0999999 V | PASS |
| Vina_max | ~100 mV | 0.0999999 V | PASS |
| Vload_min | 4.90 V | 4.9 V | PASS |
| Psh_pk | 0.2 W | 0.2 W | PASS |
| Isense_pk | 2 A | 2 A | PASS |
| Vsh_at_1p5 (t = 9 ms) | 75 mV | 0.0749998 V | PASS |

Measurement lines from docs/sim_ltspice.log (the log is UTF-16 with a BOM; shown converted):

```
vsh_max: MAX(v(sup,load))=0.0999999 FROM 0 TO 0.03
vina_max: MAX(v(inp,inn))=0.0999999 FROM 0 TO 0.03
vload_min: MIN(v(load))=4.9 FROM 0 TO 0.03
psh_pk: MAX(v(sup,load)*i(rsh))=0.2 FROM 0 TO 0.03
isense_pk: MAX(v(sup,load)/rshunt)=2 FROM 0 TO 0.03
vsh_at_1p5: v(sup,load)=0.0749998 at 0.009
```

*ngspice transient: load current steps (top); shunt voltage V(sup,load) and filtered INA219 input V(inp,inn) in mV (bottom).*

### ngspice 47 cross-check

```
ngspice -b sim/ngspice/shunt_frontend_ngspice.cir
python3 sim/ngspice/plot_waveforms.py
```

The netlist is ported from LTspice; dialect changes: `.tran` step syntax, `.meas` moved into a control block, and no `plotwinsize`. Result from docs/sim_ngspice.log (PASS: rel <= 0.1 % or abs <= 1e-6):

| Check | LTspice | ngspice | Diff | Rel % | Result |
|---|---|---|---|---|---|
| Vsh_max | 0.0999999 | 0.1 | 1.0e-07 | 0.0001 | PASS |
| Vina_max | 0.0999999 | 0.1 | 1.0e-07 | 0.0001 | PASS |
| Vload_min | 4.9 | 4.9 | 0 | 0.0000 | PASS |
| Psh_pk | 0.2 | 0.2 | 0 | 0.0000 | PASS |
| Isense_pk | 2 | 2 | 0 | 0.0000 | PASS |
| Vsh_at_1p5 | 0.0749998 | 0.075 | 2.0e-07 | 0.0003 | PASS |

6/6 within 0.1 % of LTspice. Max residual of V(sup,load), LTspice minus ngspice, on a 1 us grid: 0.023 uV (at t = 18.1010 ms).

Comparison block from docs/sim_ngspice.log:

```
# Comparison ngspice vs LTspice (PASS: rel <= 0.1 % or abs <= 1e-6)
measurement        LTspice       ngspice         diff     rel %  result
Vsh_max          0.0999999           0.1    1.000e-07    0.0001  PASS
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
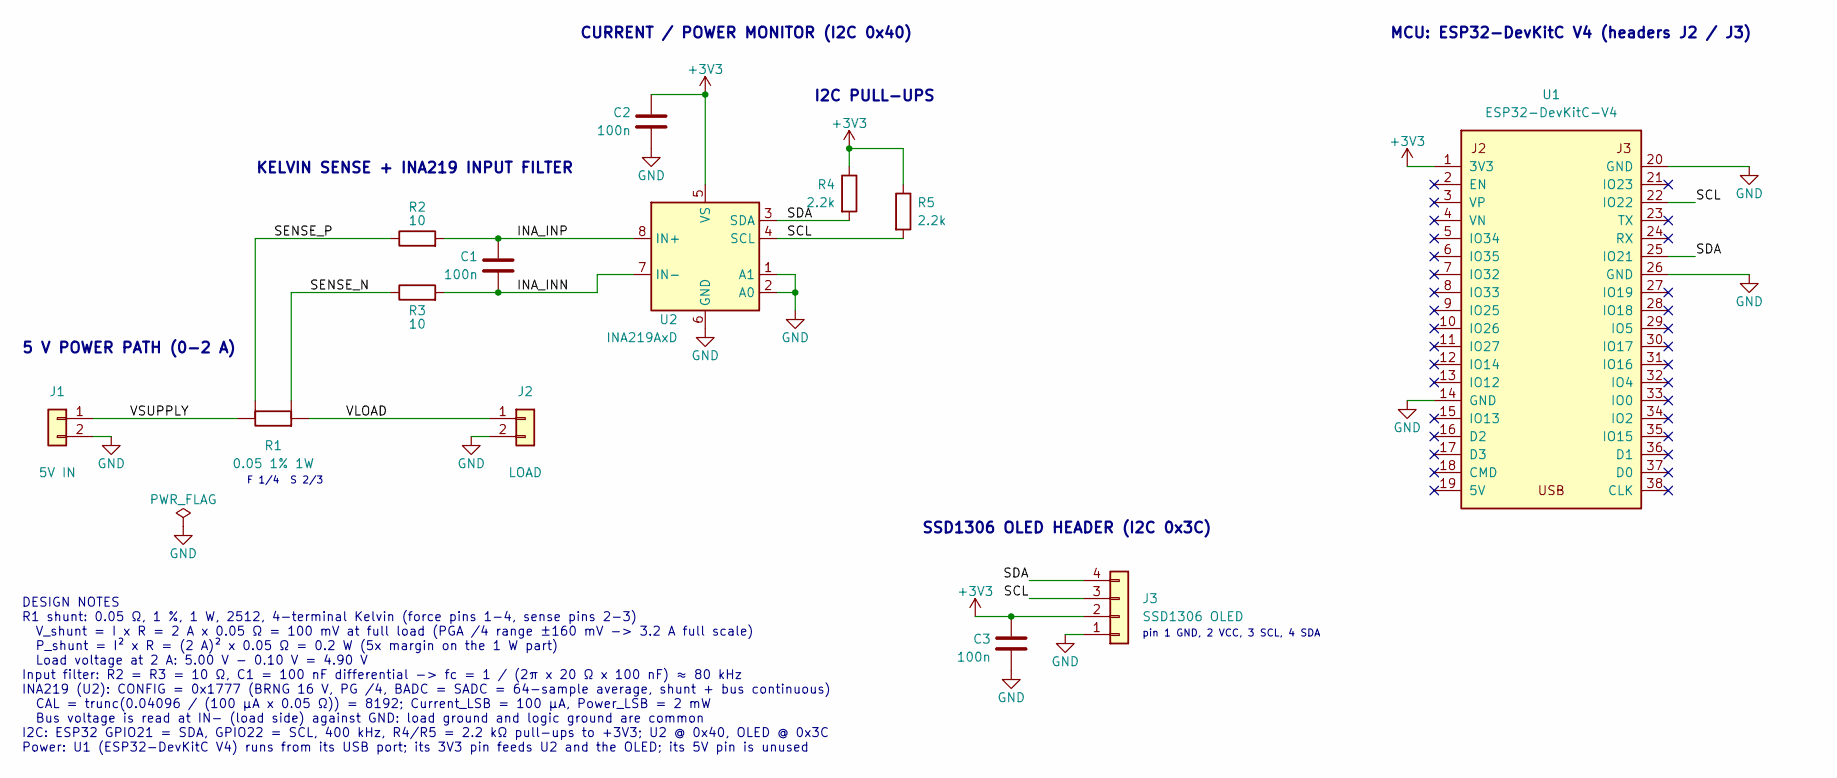
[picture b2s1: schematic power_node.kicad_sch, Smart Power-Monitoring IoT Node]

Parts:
C1, C2, C3: 100n; C_0603_1608Metric
J1: 5V IN; PinHeader_1x02_P2.54mm_Vertical
J2: LOAD; PinHeader_1x02_P2.54mm_Vertical
J3: SSD1306 OLED; PinHeader_1x04_P2.54mm_Vertical
R1: 0.05 1% 1W; R_Shunt_Vishay_WSK2512_6332Metric_T1.19mm
R2, R3: 10; R_0603_1608Metric
R4, R5: 2.2k; R_0603_1608Metric
U1: ESP32-DevKitC-V4; ESP32-DevKitC-V4_Socket
U2: INA219AxD; SOIC-8_3.9x4.9mm_P1.27mm

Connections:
+3V3: C2.1, C3.1, J3.2, R4.1, R5.1, U1.1 (3V3), U2.5 (VS)
/INA_INN: C1.2, R3.2, U2.7 (IN-)
/INA_INP: C1.1, R2.2, U2.8 (IN+)
/SCL: J3.3, R5.2, U1.22 (IO22), U2.4 (SCL)
/SDA: J3.4, R4.2, U1.25 (IO21), U2.3 (SDA)
/SENSE_N: R1.3, R3.1
/SENSE_P: R1.2, R2.1
/VLOAD: J2.1, R1.4
/VSUPPLY: J1.1, R1.1
GND: C2.2, C3.2, J1.2, J2.2, J3.1, U1.14 (GND), U1.20 (GND), U1.26 (GND), U2.1 (A1), U2.2 (A0), U2.6 (GND)

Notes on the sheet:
F 1/4 S 2/3
pin 1 GND, 2 VCC, 3 SCL, 4 SDA
5 V POWER PATH (0-2 A)
KELVIN SENSE + INA219 INPUT FILTER
CURRENT / POWER MONITOR (I2C 0x40)
I2C PULL-UPS
MCU: ESP32-DevKitC V4 (headers J2 / J3)
SSD1306 OLED HEADER (I2C 0x3C)
DESIGN NOTES R1 shunt: 0.05 Ω, 1 %, 1 W, 2512, 4-terminal Kelvin (force pins 1-4, sense pins 2-3) V_shunt = I x R = 2 A x 0.05 Ω = 100 mV at full load (PGA /4 range ±160 mV -> 3.2 A full scale) P_shunt = I² x R = (2 A)² x 0.05 Ω = 0.2 W (5x margin on the 1 W part) Load voltage at 2 A: 5.00 V - 0.10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

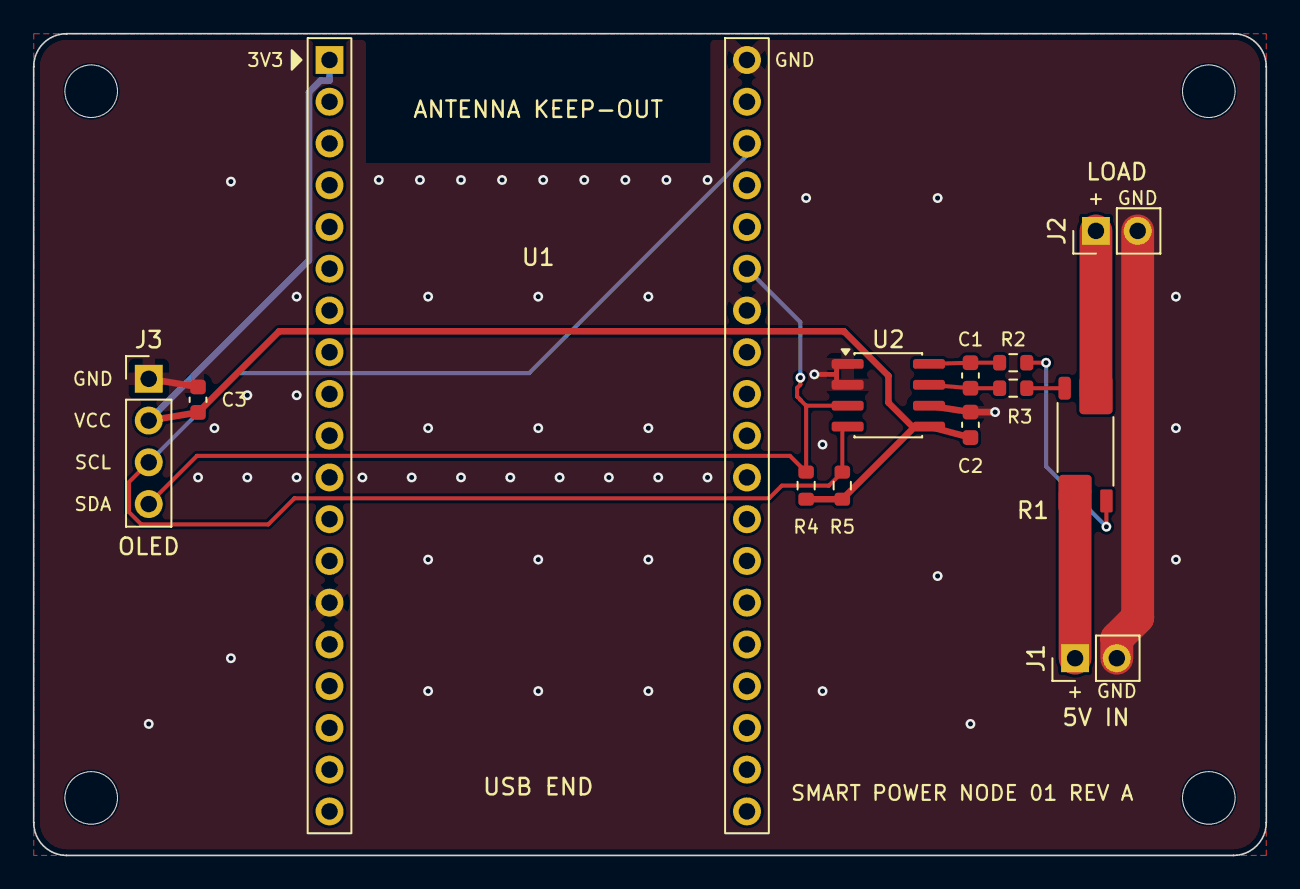
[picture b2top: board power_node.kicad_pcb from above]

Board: 2 copper layers, 75.0 x 50.0 mm, 17 parts (0 on the bottom side), 10 nets.

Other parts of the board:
H1, H2, H3, H4: MountingHole_3.2mm_M3

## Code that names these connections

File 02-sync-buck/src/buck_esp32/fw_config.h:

// fw_config.h - firmware-only constants for buck_esp32 (the controller's own numbers live in
// src/buck_ctrl/buck_config.h and are not repeated here).
#pragma once

// Pin map (ESP32 header J3)
#define PIN_PWM_H            18   // -> UCC27211 HI (high-side gate)
#define PIN_PWM_L            19   // -> UCC27211 LI (low-side gate)
// ADC1: GPIO34 = ADC1_CH6 (VSENSE), GPIO35 = ADC1_CH7 (ISENSE), GPIO33 = ADC1_CH5 (VINSENSE)

// Simulator build (FW_SIM_WOKWI). The LEDC variant is the Wokwi build (pwm_backend.h), so it also
// selects the simulator-only paths below; hardware builds (MCPWM) never define it. Measured in
// Wokwi (sim/wokwi/README_WOKWI.md):
//   - three adc_oneshot_read calls take 128 us of simulated time (budget 20 us) and Wokwi's raw
//     code is V x 4095 / 5.0 V whatever the simulated eFuse says (adc_sense.cpp);
//   - one control update costs about 91 us of simulated time (buck_update alone 15 us), and the
//     50 kHz gptimer interrupt stretches it to about 500 us (about 16 us of every 20 us goes to
//     the interrupt), so a 20 us loop cannot run there at all (docs/wokwi_timing_diag.log).
// So the sim build runs the same discrete-time loop slowed down by FW_SIM_TIME_SCALE: one update
// every 20 us x scale of simulated time, paced on the CPU cycle counter (no interrupt), and the
// buck_plant chip integrates its model with dt / scale, so plant and controller see exactly
// 20 us per update. Firmware times (t_us, settle_us, trip_us) are control time: 20 us per tick.
#if defined(BUCK_PWM_LEDC) && !defined(FW_SIM_WOKWI)
#define FW_SIM_WOKWI         1
#endif
#if defined(FW_SIM_WOKWI) && !defined(FW_SIM_TIME_SCALE)
#define FW_SIM_TIME_SCALE    20       // must match the chip's timeScale attribute (diagram.json)
#endif

// Serial: 921600 baud 8N1. At 115200 the 100 us capture window (about 40 bytes per row,
// 10 rows per ms) needs about 35 ms of UART time per 1 ms captured; 921600 drains a 50-row
// window in about 22 ms, so back-to-back load steps 50 ms apart are printed without drops.
#define FW_BAUD              921600
#define FW_TX_BUF            4096

// Tasks: control on core 1 (the gptimer ISR is allocated from it, so it fires on core 1 too),
// telemetry on core 0 at low priority so UART work never competes with the loop.
#define FW_CTRL_CORE         1
#define FW_CTRL_PRIO         (configMAX_PRIORITIES - 2)
#define FW_CTRL_STACK        4096
#define FW_TELEM_CORE        0
#define FW_TELEM_PRIO        1
#define FW_TELEM_STACK       4096

// Control tick: gptimer at 1 MHz, alarm every 20 counts = BUCK_TS_S (20 us, 50 kHz)
#define FW_TICK_RES_HZ       1000000
#define FW_TICK_COUNTS       20

// Overrun fault when this many control ticks were missed in a row. The count is of missed
// ticks, not of late updates: one update that stalls for N ticks adds N, and a stall of
// N >= FW_OVERRUN_LIMIT ticks latches on its own (the notification count collapses the missed
// ticks into one late update, so counting updates would lose them). Updates with no overrun
// reset the count.
// N = 3 matches the OCP debounce (BUCK_OCP_SAMPLES = 3, 60 us): one isolated late tick only
// delays one duty change by 20 us and is harmless, but three in a row means the loop has run
// late for the whole OCP window, so the firmware can no longer promise the over-current
// response it was designed for and shuts the stage down.
#ifndef FW_OVERRUN_LIMIT
#define FW_OVERRUN_LIMIT     3
#endif

// Test build only: -DFW_TEST_STALL_TICKS=n busy-waits n control ticks inside one update (once,
// after FW_TEST_STALL_AT_US of control time) to prove the overrun latch catches a single stall.
#ifdef FW_TEST_STALL_TICKS
#ifndef FW_TEST_STALL_AT_US
#define FW_TEST_STALL_AT_US  20000
#endif
#endif

// Trace decimation (in control updates of 20 us)
#define FW_FAST_DIV          5        // 100 us: one trace sample = mean of 5 control samples
#define FW_BG_DIV            500      // 10 ms background trace
#define FW_CAP_PRE           10       // capture window: 1 ms before the trigger ...
#define FW_CAP_POST          40       // ... and 4 ms after it (extended on re-trigger)
#define FW_DI_TRIG_A         0.5f     // |change of il| between 100 us samples that triggers
#define FW_DI_START_A        0.1f     // a row that moved by more than this already holds the step start
#define FW_BAND_FRAC         0.01f    // +/-1 % of BUCK_VOUT_REF_V
// Load-step pass limits, the same as the host test (test_buck_ctrl.c): dip >= 4.50 V,
// release peak <= 5.50 V, recovery to +/-1 % within 5 ms. The STEP line ends in STEP_OK or STEP_FAIL.
#define FW_STEP_VMIN_V       4.50f
#define FW_STEP_VMAX_V       5.50f
#define FW_STEP_SETTLE_MAX_US 5000
#define FW_SETTLE_HOLD_US    2000     // in band this long = settled
#define FW_STEP_TIMEOUT_US   50000    // STEP event gives up after this (settle_us = -1)
#ifndef FW_STAT_DIV
#ifdef FW_SIM_WOKWI
#define FW_STAT_DIV          1000     // 20 ms of control time (0.4 s simulated at scale 20)
#else
#define FW_STAT_DIV          50000    // 1 s STAT line
#endif
#endif

// Telemetry ring (single producer = control task, single consumer = telemetry task)
#define FW_RING_LEN          512      // power of two
#define FW_RING_RESERVE      16       // slots only events may use, so a FAULT is never dropped
